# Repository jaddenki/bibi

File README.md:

# bibi

bibi is a benchtop buddy that can cruise around your desk. it has two modules that you can interchange, allowing bibi to either wipe down or vacuum your desk!

bibi will also use sensors for obstacle detection and edge avoidance, with a little face on a display so it can show system feedback and have some personality while it works.  

love u bb <3

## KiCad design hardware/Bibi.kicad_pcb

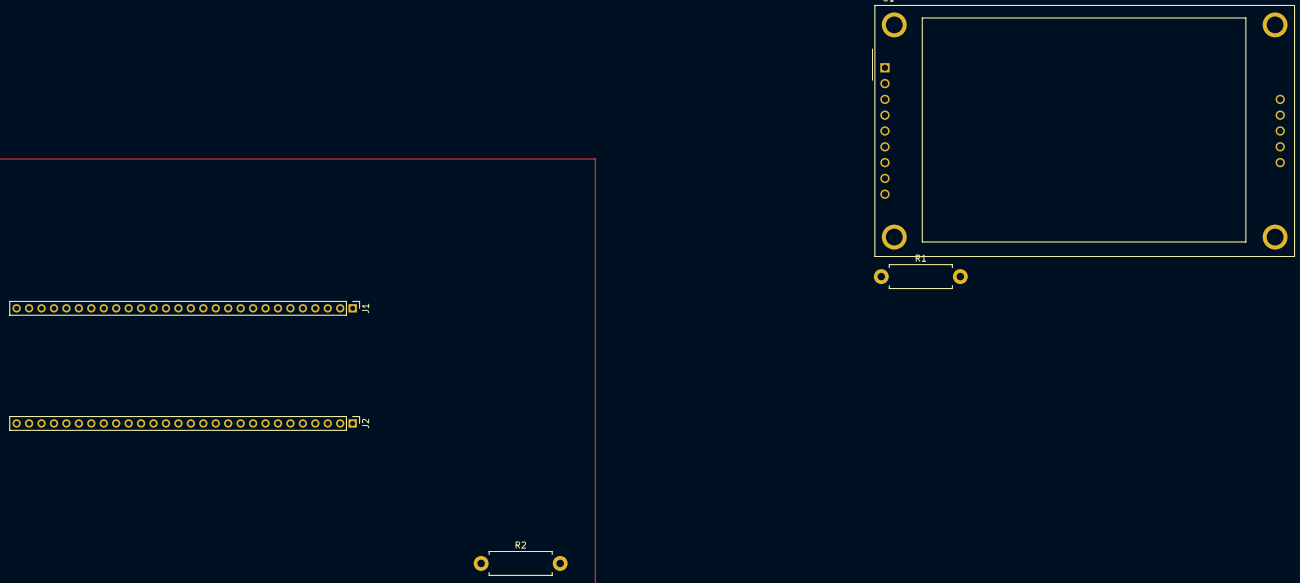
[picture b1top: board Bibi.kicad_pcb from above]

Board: 2 copper layers, 5 parts (0 on the bottom side), 8 nets, no tracks yet.

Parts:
J1, J2: PinHeader_1x28_P2.00mm_Vertical
R1: 1.5K; R_Axial_DIN0411_L9.9mm_D3.6mm_P12.70mm_Horizontal
R2: 6.8K; R_Axial_DIN0411_L9.9mm_D3.6mm_P12.70mm_Horizontal
U1: CR2013-MI2120

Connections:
/3.3V: J1.2, J2.2, U1.1 (VCC), U1.8 (LED)
/5V: J1.1, J2.1, R1.2, R2.1
/12: J1.15, U1.4 (RESET)
/13: J1.16, U1.3 (~CS)
/14: J1.17, U1.7 (SCK)
/15: J1.18, U1.6 (MOSI)
/17: J1.20, U1.5 (D/~C)
GND: J1.28, J2.28, R2.2, U1.2 (GND)

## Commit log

2025-10-03 fix spacing
2025-10-03 BIBI
2025-10-30 add pico sdc submodule and gitigonre
2025-10-30 serving face (idle anim)
2025-10-30 repo organization
2025-10-30 update screen plan
2025-10-30 hardware heh
2025-10-30 add footprints
2025-10-31 pcb file started
2025-10-31 ir sensor code
2025-11-03 auto driving algorithm framework
2025-11-05 new wiring
2025-11-07 multiple facial expressions
2025-11-07 anim change on ir sensor test #5
2025-11-14 rikas first push
2025-11-17 implement DMA! yay!
2025-11-17 updated schematic
2025-11-17 update config to current pins
2025-11-17 bb test
2025-11-17 fixed includes, added state.h for turning boolean, added adc functions
2025-11-20 auto movement done
2025-11-21 random pwm for fan, controlled by button
2025-11-21 rotate face & fix includes
2025-11-21 bool added for button spamming
2025-11-30 upload bibody
2025-12-01 schema update
2025-12-03 integration
2025-12-03 change pinout and more integration
2025-12-03 integrate face!
2025-12-03 movement update
2025-12-04 gamblibi
2025-12-04 add gamblibi to irq handler
2025-12-05 gamblibi anim
2025-12-05 printing changes
2025-12-05 adc_run added
2025-12-05 fixed i guess lol
2025-12-05 updated rand timer to match animation
2025-12-05 gamblibi turst
2025-12-05 changed starting fan speed
2025-12-05 tft driver update
2025-12-05 asdfasdf
2025-12-05 freak u adc run
2025-12-05 perma delete
2025-12-05 threshold changed to 0.2V
2025-12-05 misc changes
2025-12-05 auto movement back
2025-12-05 change pins and the such
2025-12-11 Add hello message to hi.md
